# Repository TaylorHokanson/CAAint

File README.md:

# CAAint
An open source badge project for noobs, artists, and the interdimensionally-curious

1. [Project Goals](#project-goals)
2. [BOM](#bom)
2. [Design](#design)
2. [Inspiration](#inspiration)
3. [Team](#team)
4. [Thanks](#thanks)

## Project Goals
We are artists following in the footsteps of the DEFCON [Badgelife](https://hackaday.com/tag/badgelife/) scene. Badgelifers create custom electronic devices to replace the ho-hum badges that display your name and affiliation at conferences. These badges feature playable video games, animated LED displays, wifi connectivity, and more! But what would happen if we released a simple badge template that non-engineers could program and expand upon themselves? Let's find out.

## BOM
After [much experimentation](/Archive), we've settled on [this board](https://www.aliexpress.com/item/TTGO-ESP8266-ESP32-0-96-0-96-inch-OLED-Display-WiFi-Bluetooth-18650-Lithium-Battery-Shield/32839517061.html?spm=a2g0s.9042311.0.0.qXU7bh). It includes the following features in one tidy package:

1. Wifi/bluetooth (via ESP32, the recent update to the ESP8266)
2. LIPO battery clip/recharging circuit
3. Arduino IDE compatibility
4. OLED screen

## Design
After flirting with building a project from scratch, we've brought the process back down to earth. Right now the plan is to focus on a cool little breakout for an existing ESP PCB (see [BOM](#bom)) that will allow for the addition of sensors etc. in the form of pluggable modules. The form-factor could even take the shape of a robot or action figure! Once we release the platform specs, other developers could develop their own modules to extend the project's ecosystem. Ideas include:

1. [Co-planar PCB connectors](https://www.gradconn.com/Products/BoardToBoard/CoPlanarConnectors) ([image](/Media/right_angle_to_right_angle.jpg))
2. [Hemaphroditic connectors](https://octopart.com/10120045-400lf-fci-29441219) ([image](/Media/10120045-400LF.jpg))
3. [5-way tac switch](https://www.aliexpress.com/wholesale?catId=0&initiative_id=AS_20180403080800&SearchText=5+way+tactile+switch)

## Inspiration

1. [P-O-X](https://en.wikipedia.org/wiki/P-O-X) (thanks Paul!)

## Team
Nick Bontrager, Texas Christian University  
Taylor Hokanson, Columbia College Chicago

...and you? Please get in touch!

## Thanks
Supported in part by a generous [Faculty Development Grant](https://about.colum.edu/faculty-development/awards-grants/full-time-development-grants.html) from Columbia College Chicago

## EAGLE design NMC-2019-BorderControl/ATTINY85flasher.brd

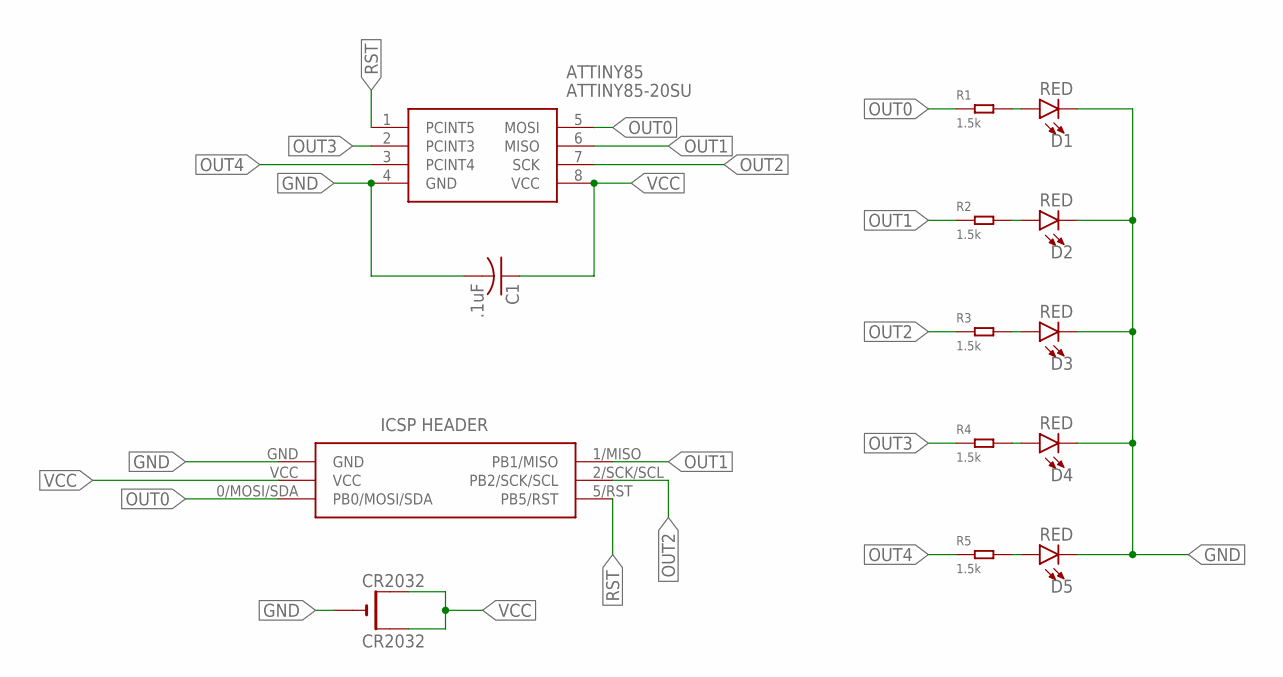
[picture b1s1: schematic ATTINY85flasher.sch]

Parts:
ATTINY85: ATTINY85-20SU; SOT127P798X216-8N
C1: .1uF; C0603
CR2032: CR2032; CR2032-SMD
D1, D2, D3, D4, D5: RED; LED-1206
J1: ICSP-LO-SILK
R1, R2, R3, R4, R5: 1.5k; R1206

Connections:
GND: ATTINY85.4 (GND), C1.2, CR2032.-, D1.C, D2.C, D3.C, D4.C, D5.C, J1.GND
unnamed: D5.A, R5.2
unnamed: D4.A, R4.2
unnamed: D3.A, R3.2
unnamed: D2.A, R2.2
unnamed: D1.A, R1.2
OUT0: ATTINY85.5 (MOSI), J1.0/MOSI/SDA (PB0/MOSI/SDA), R1.1
OUT1: ATTINY85.6 (MISO), J1.1/MISO (PB1/MISO), R2.1
OUT2: ATTINY85.7 (SCK), J1.2/SCK/SCL (PB2/SCK/SCL), R3.1
OUT3: ATTINY85.2 (PCINT3), R4.1
OUT4: ATTINY85.3 (PCINT4), R5.1
RST: ATTINY85.1 (PCINT5), J1.5/RST (PB5/RST)
VCC: ATTINY85.8 (VCC), C1.1, CR2032.+$1 (+), CR2032.+$2 (+1), J1.VCC

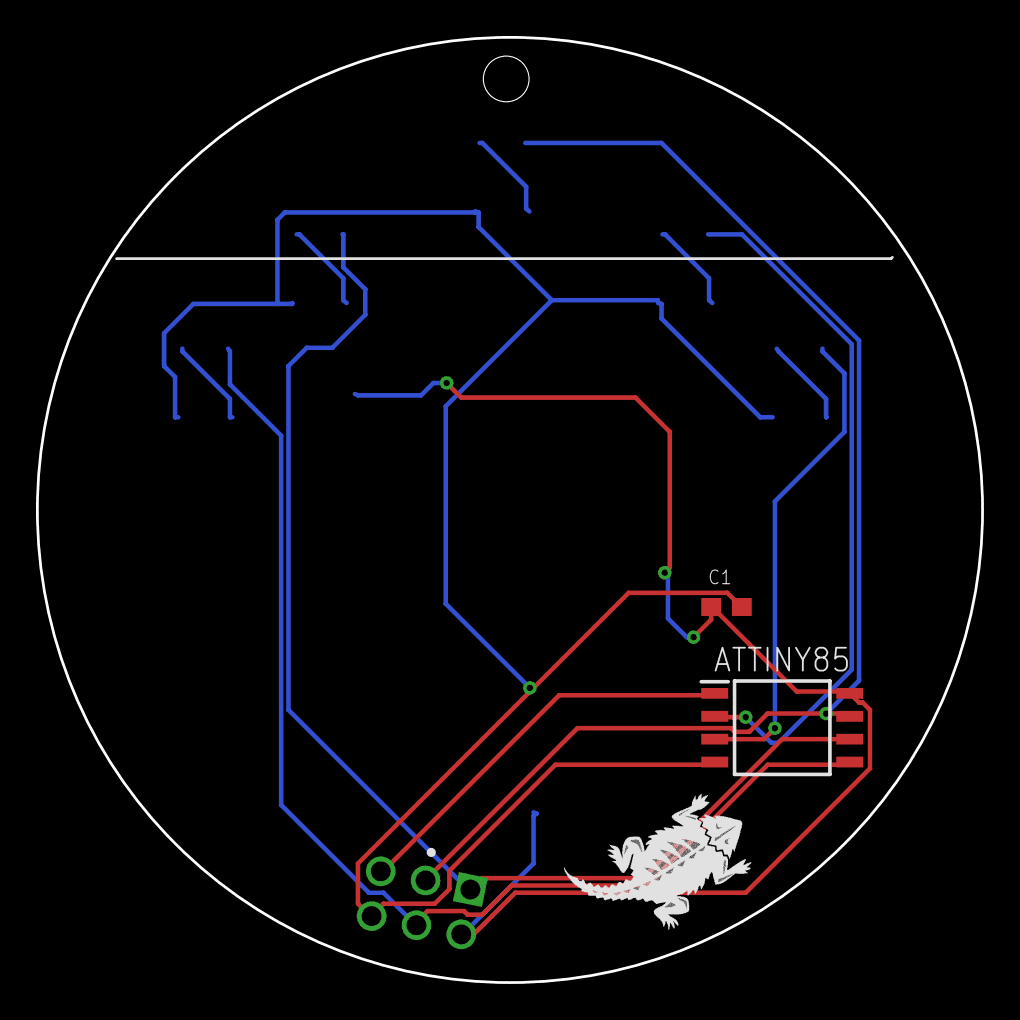
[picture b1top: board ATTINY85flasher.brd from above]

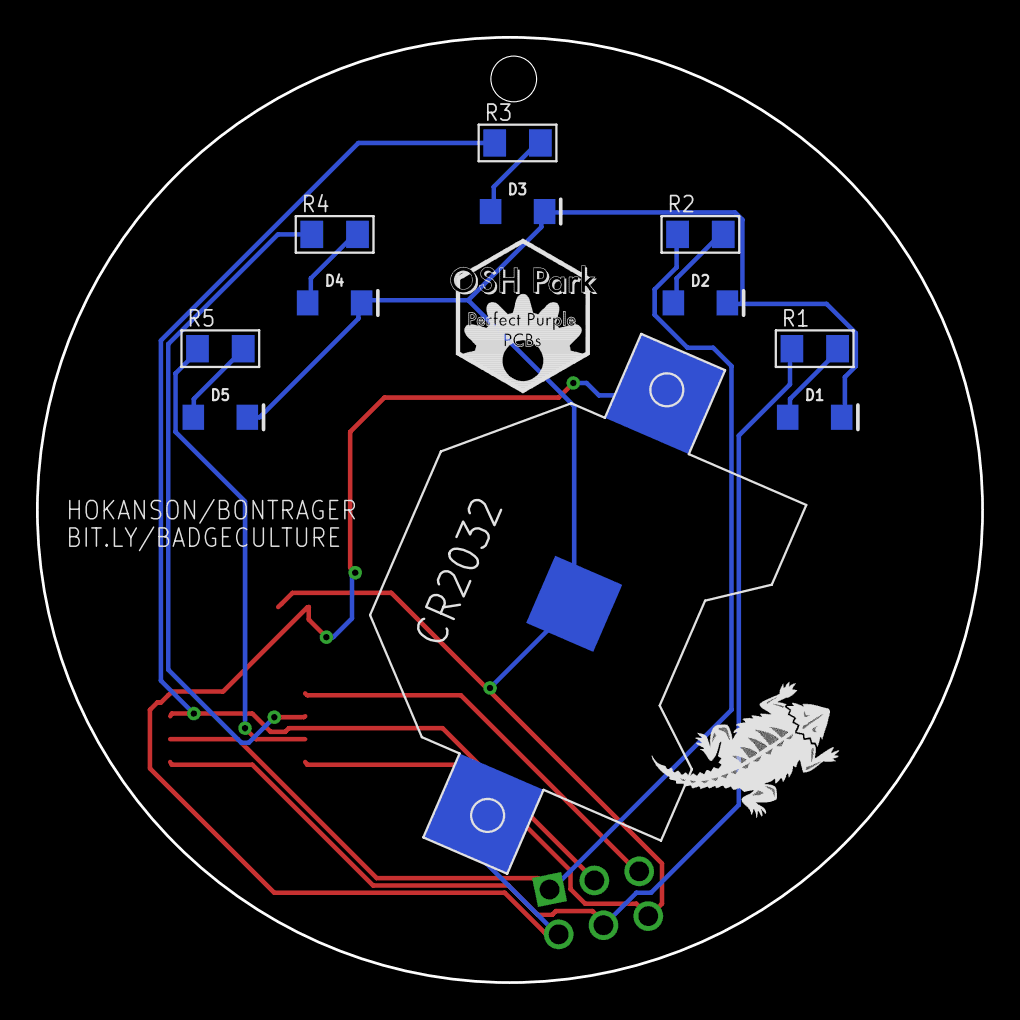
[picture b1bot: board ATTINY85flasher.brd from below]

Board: 2 copper layers, 52.5 x 52.5 mm, 17 parts (13 on the bottom side), 13 nets.

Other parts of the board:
U$1: OSHPARK_LOGOHEX
U$2, U$3: HORNEDFROG

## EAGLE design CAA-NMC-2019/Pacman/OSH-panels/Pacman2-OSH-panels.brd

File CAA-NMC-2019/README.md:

Useful stuff:

MOVE (>0 0) (X Y); to move groups to a new relative X Y position

Board now centered on origin. Use 16.666, 8.333, 4.166, 2.083, and 1.042 grids for general placement.

Changes:

Cleaned up library. Most parts are now defined at library level, including protogrid and power rails. Made custom definition of RGB LEDs so that I could include the cap footprint, this helps prevent endless dragging of multiple parts during layout experiementation. Left the original set in place so that we can verify the wiring transferred OK. Added a switch and two styles of battery mount, switch should isolate bat from USB if both are present (though please check up on my work).

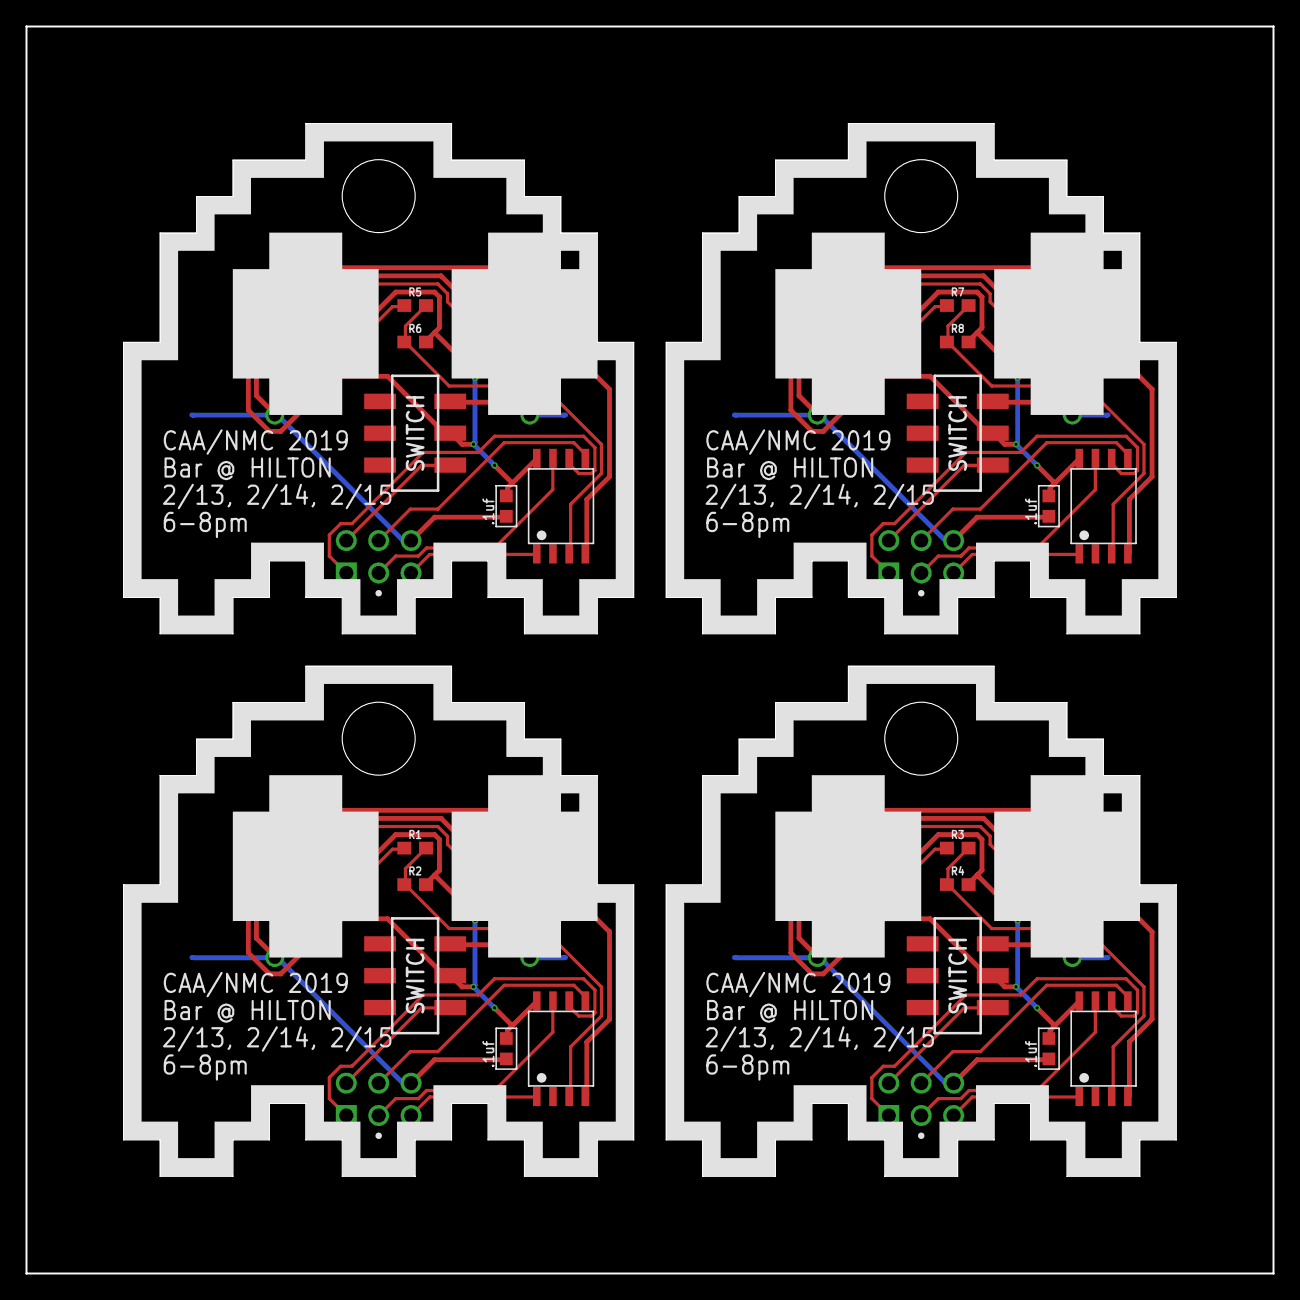
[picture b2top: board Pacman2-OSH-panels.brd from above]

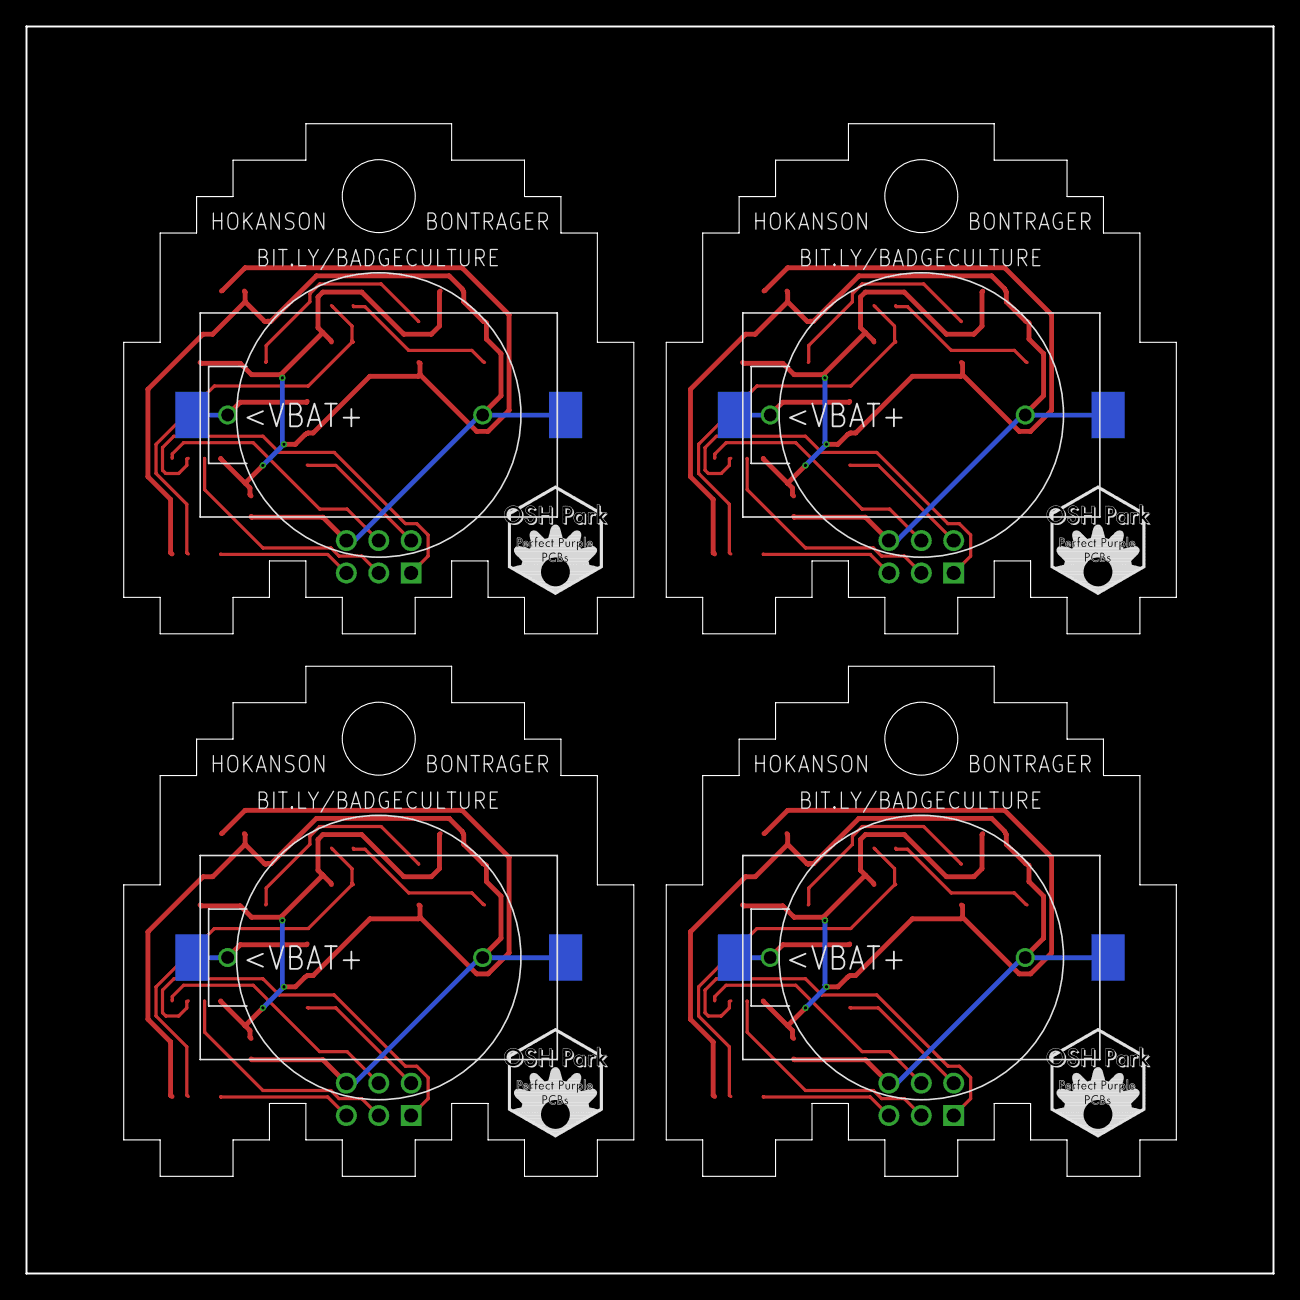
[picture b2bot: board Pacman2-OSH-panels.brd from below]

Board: 2 copper layers, 97.8 x 97.8 mm, 44 parts (12 on the bottom side), 44 nets.

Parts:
D1, D2, D3, D4, D5, D6, D7, D8: WS2812B
DECOUPLER, DECOUPLER1, DECOUPLER2, DECOUPLER3: .1uf; 0603-CAP
IC1, IC2, IC3, IC4: ATTINY85-20SU; SOT127P798X216-8N
J1, J2, J3, J4: ICSP-LO-SILK
R1, R3, R5, R7: 470; 0603
R2, R4, R6, R8: 10k; 0603
U$1, U$8, U$12, U$145: SMT-SWITCH
U$2, U$4, U$9, U$13: SMT-BATTERY-HOLDER; SMT-CR-HOLDER
U$3, U$6, U$10, U$14: THRU-CR-HOLDER
U$5, U$7, U$11, U$15: OSHPARK_LOGOHEX

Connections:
GND: D1.CAP1, D1.GND, D2.CAP1, D2.GND, DECOUPLER.CAP1, IC1.GND, J2.GND, U$2.GND, U$3.GND
GND1: D3.CAP1, D3.GND, D4.CAP1, D4.GND, DECOUPLER1.CAP1, IC2.GND, J1.GND, U$4.GND, U$6.GND
GND2: D5.CAP1, D5.GND, D6.CAP1, D6.GND, DECOUPLER2.CAP1, IC3.GND, J3.GND, U$9.GND, U$10.GND
GND3: D7.CAP1, D7.GND, D8.CAP1, D8.GND, DECOUPLER3.CAP1, IC4.GND, J4.GND, U$13.GND, U$14.GND
unnamed: D3.DO, D4.DI
unnamed: D3.DI, R3.1
unnamed: D1.DO, D2.DI
unnamed: D5.DO, D6.DI
unnamed: D1.DI, R1.1
unnamed: D5.DI, R5.1
unnamed: D7.DO, D8.DI
unnamed: D7.DI, R7.1
PB0: IC1.PB0, J2.0/MOSI/SDA
PB1: IC1.PB1, J2.1/MISO
PB2: IC1.PB2, J2.2/SCK/SCL
PB4: IC1.PB4, R1.2, R2.1
PB5: IC1.PB5, J2.5/RST
PB6: IC2.PB0, J1.0/MOSI/SDA
PB8: IC2.PB4, R3.2, R4.1
PB9: IC2.PB2, J1.2/SCK/SCL
PB10: IC2.PB5, J1.5/RST
PB11: IC2.PB1, J1.1/MISO
PB12: IC3.PB0, J3.0/MOSI/SDA
PB14: IC3.PB4, R5.2, R6.1
PB15: IC3.PB2, J3.2/SCK/SCL
PB16: IC3.PB5, J3.5/RST
PB17: IC3.PB1, J3.1/MISO
PB18: IC4.PB0, J4.0/MOSI/SDA
PB20: IC4.PB4, R7.2, R8.1
PB21: IC4.PB2, J4.2/SCK/SCL
PB22: IC4.PB5, J4.5/RST
PB23: IC4.PB1, J4.1/MISO
VBAT: U$2.VBAT, U$3.VBAT, U$145.4
VBAT1: U$1.4, U$4.VBAT, U$6.VBAT
VBAT2: U$8.4, U$9.VBAT, U$10.VBAT
VBAT3: U$12.4, U$13.VBAT, U$14.VBAT
VCC: D1.CAP2, D1.VCC, D2.CAP2, D2.VCC, DECOUPLER.CAP2, IC1.VCC, R2.2, U$145.5
VCC1: D3.CAP2, D3.VCC, D4.CAP2, D4.VCC, DECOUPLER1.CAP2, IC2.VCC, R4.2, U$1.5
VCC2: D5.CAP2, D5.VCC, D6.CAP2, D6.VCC, DECOUPLER2.CAP2, IC3.VCC, R6.2, U$8.5
VCC3: D7.CAP2, D7.VCC, D8.CAP2, D8.VCC, DECOUPLER3.CAP2, IC4.VCC, R8.2, U$12.5
VUSB: J2.VCC, U$145.6
VUSB1: J1.VCC, U$1.6
VUSB2: J3.VCC, U$8.6
VUSB3: J4.VCC, U$12.6

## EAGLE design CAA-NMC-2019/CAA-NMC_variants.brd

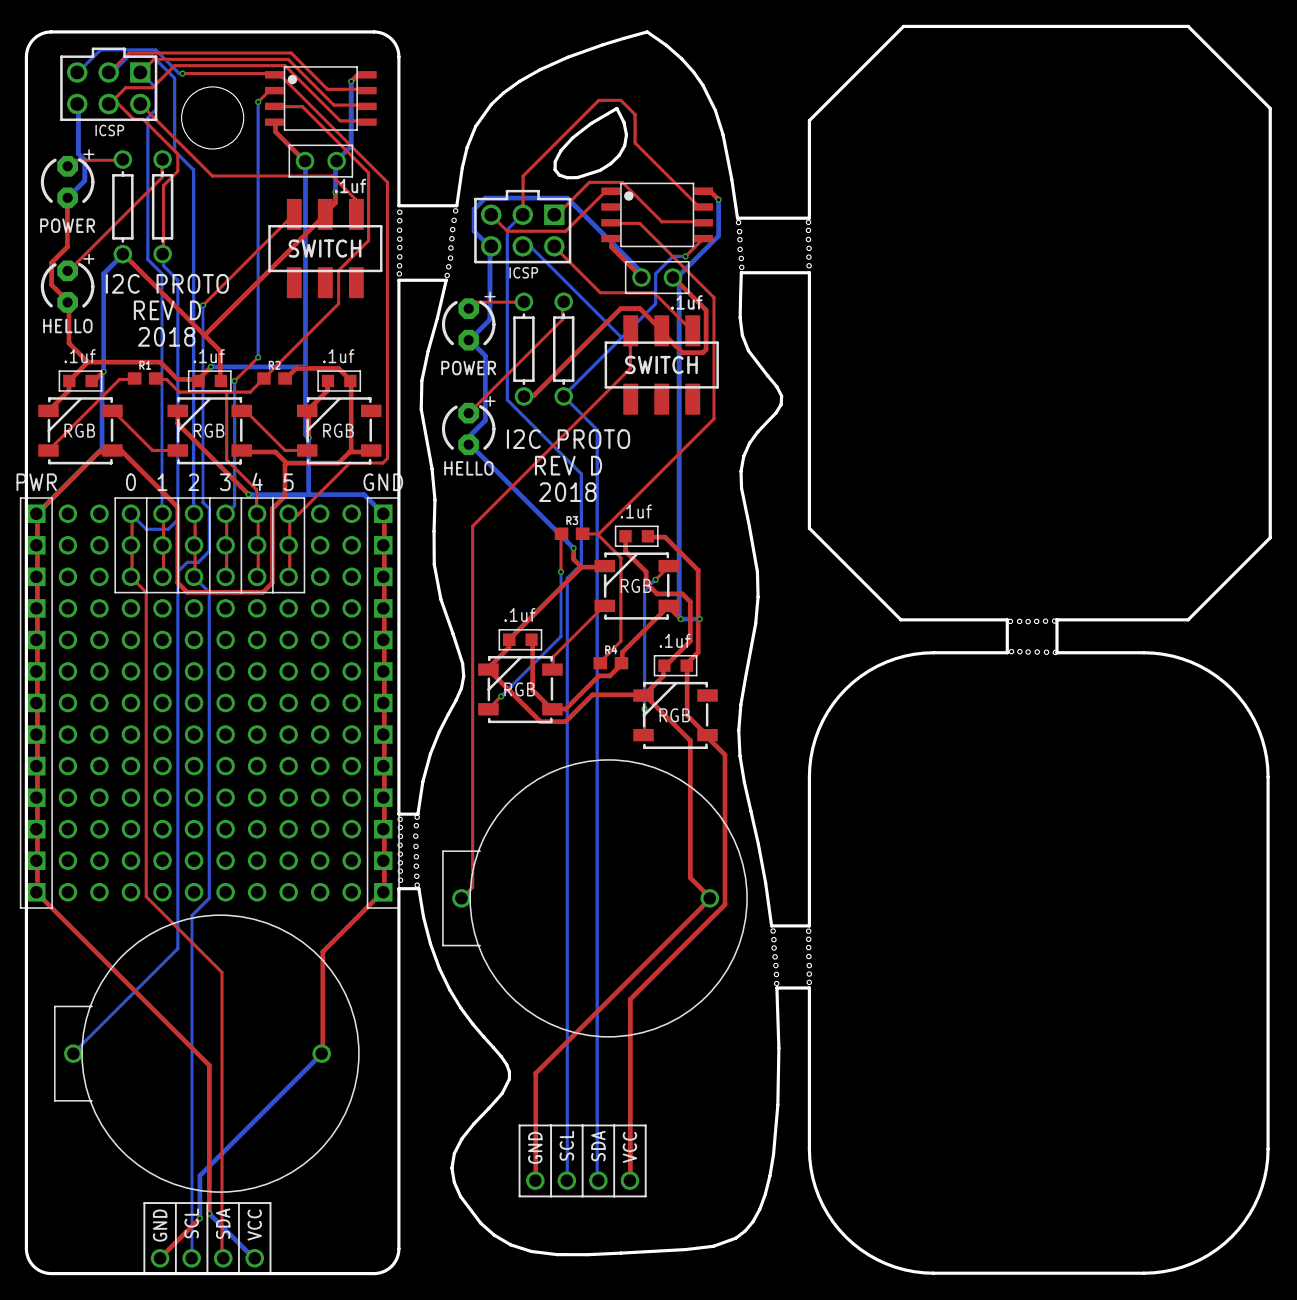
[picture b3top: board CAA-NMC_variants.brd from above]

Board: 2 copper layers, 100.2 x 100.4 mm, 37 parts (0 on the bottom side), 29 nets.

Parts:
D1, D2, D3, D4, D5, D6: WS2812B
HELLO, HELLO1: LED3MM
IC1, IC2: ATTINY85-20SU; SOT127P798X216-8N
J1, J2: M20-9980346; HDRV6W64P254_2X3_762X508X868P
POWER, POWER1: LED3MM
R1, R3: 470; 0603
R2, R4: 10k; 0603
U$1: PROTO
U$3, U$14: THRU-CR-HOLDER
U$4, U$71: GND; 1X01
U$5, U$74: VCC; 1X01
U$6, U$72: SDA; 1X01
U$7, U$73: SCL; 1X01
U$8, U$123: DECOUPLING_CAP
U$9, U$10, U$126, U$127: RESISTOR; AXIAL-0.3
U$11, U$145: SMT-SWITCH

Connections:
GND: D1.CAP1, D1.GND, D2.CAP1, D2.GND, D3.CAP1, D3.GND, HELLO.NEG, IC1.GND, J1.GND, POWER.NEG, U$1.GND0, U$1.GND1, U$1.GND2, U$1.GND3, U$1.GND4, U$1.GND5, U$1.GND6, U$1.GND7, U$1.GND8, U$1.GND9, U$1.GND10, U$1.GND11, U$1.GND12, U$3.GND, U$71.P$1, U$123.P$1
GND1: D4.CAP1, D4.GND, D5.CAP1, D5.GND, D6.CAP1, D6.GND, HELLO1.NEG, IC2.GND, J2.GND, POWER1.NEG, U$4.P$1, U$8.P$1, U$14.GND
unnamed: POWER.POS, U$126.P$3
unnamed: HELLO.POS, U$127.P$3
unnamed: D1.DO, D2.DI
unnamed: D2.DO, D3.DI
unnamed: D1.DI, R1.1
unnamed: POWER1.POS, U$9.P$3
unnamed: HELLO1.POS, U$10.P$3
unnamed: D4.DO, D5.DI
unnamed: D5.DO, D6.DI
unnamed: D4.DI, R3.1
PB0: IC1.PB0, J1.0/MOSI/SDA, U$1.0A, U$1.0B, U$1.0C, U$72.P$1, U$127.P$4
PB1: IC1.PB1, J1.1/MISO, U$1.1A, U$1.1B, U$1.1C
PB2: IC1.PB2, J1.2/SCK/SCL, U$1.2A, U$1.2B, U$1.2C, U$73.P$1
PB3: IC1.PB3, U$1.3A, U$1.3B, U$1.3C
PB4: IC1.PB4, R1.2, R2.1, U$1.4A, U$1.4B, U$1.4C
PB5: IC1.PB5, J1.5/RST, U$1.5A, U$1.5B, U$1.5C
PB6: IC2.PB0, J2.0/MOSI/SDA, U$6.P$1, U$10.P$4
PB8: IC2.PB4, R3.2, R4.1
PB9: IC2.PB2, J2.2/SCK/SCL, U$7.P$1
PB10: IC2.PB5, J2.5/RST
PB11: IC2.PB1, J2.1/MISO
VBAT: U$3.VBAT, U$145.4
VBAT1: U$11.4, U$14.VBAT
VCC: D1.CAP2, D1.VCC, D2.CAP2, D2.VCC, D3.CAP2, D3.VCC, IC1.VCC, R2.2, U$1.PWR0, U$1.PWR1, U$1.PWR2, U$1.PWR3, U$1.PWR4, U$1.PWR5, U$1.PWR6, U$1.PWR7, U$1.PWR8, U$1.PWR9, U$1.PWR10, U$1.PWR11, U$1.PWR12, U$74.P$1, U$123.P$2, U$126.P$4, U$145.5
VCC1: D4.CAP2, D4.VCC, D5.CAP2, D5.VCC, D6.CAP2, D6.VCC, IC2.VCC, R4.2, U$5.P$1, U$8.P$2, U$9.P$4, U$11.5
VUSB: J1.VCC, U$145.6
VUSB1: J2.VCC, U$11.6

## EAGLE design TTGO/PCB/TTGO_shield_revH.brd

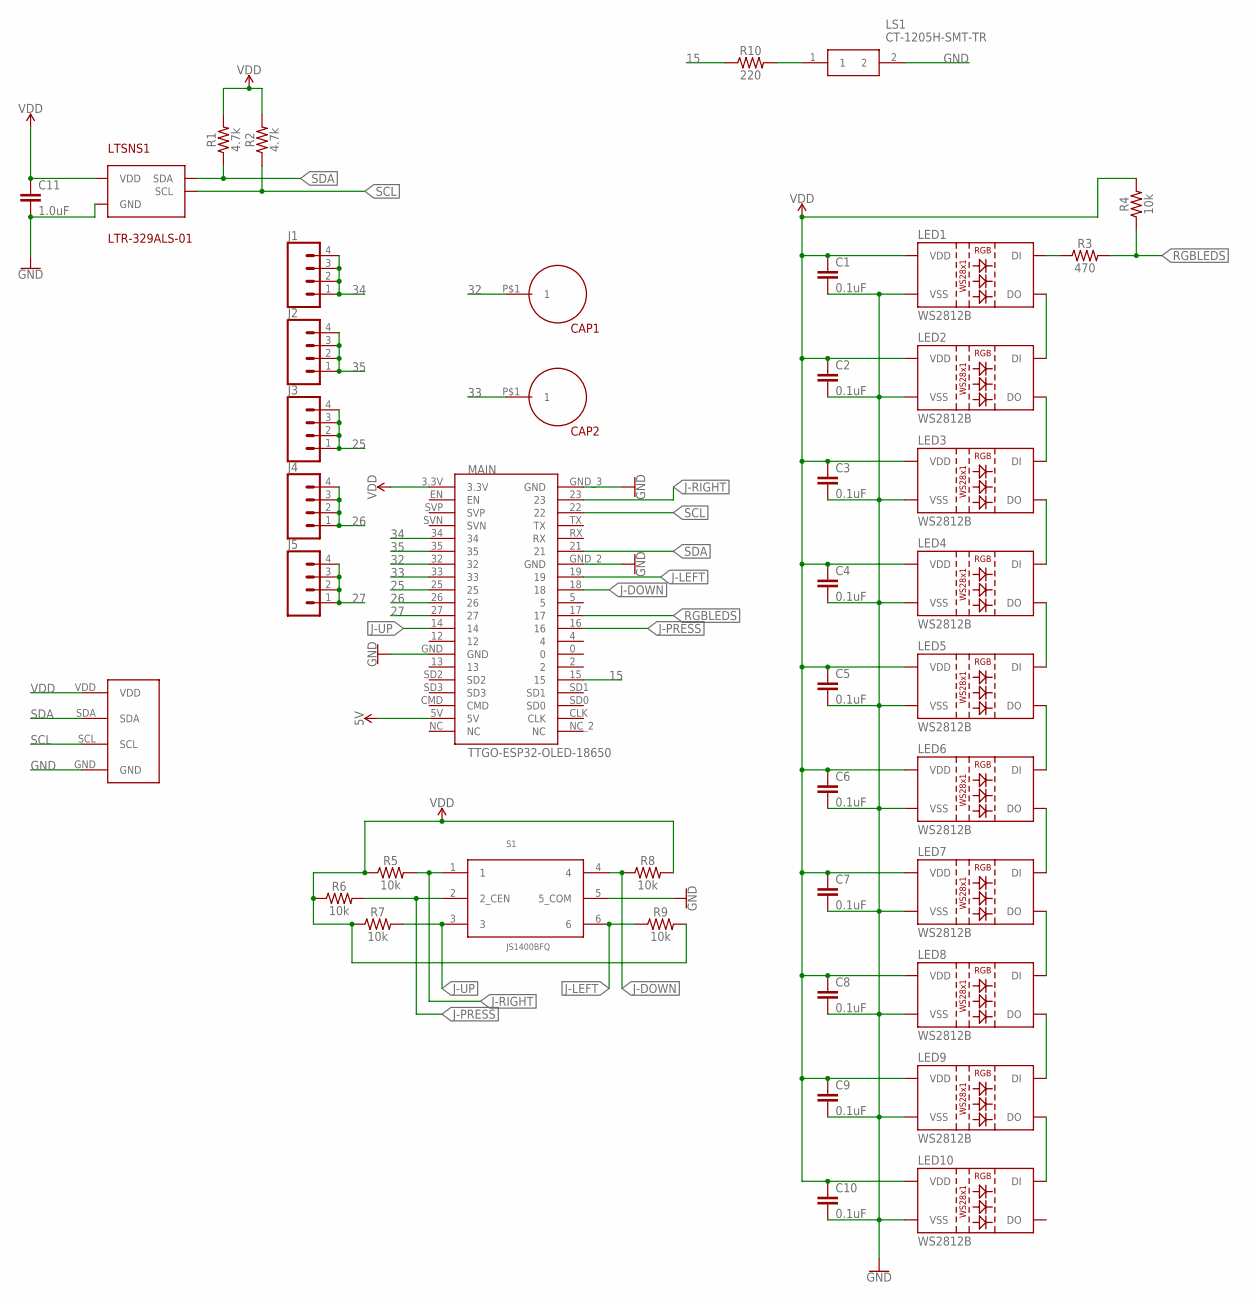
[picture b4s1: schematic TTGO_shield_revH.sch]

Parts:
C1, C2, C3, C4, C5, C6, C7, C8, C9, C10: 0.1uF; 0603
C11: 1.0uF; 0805
CAP1, CAP2: CAPSENSE_BUTTON
J1, J2, J3, J4, J5: CONN_04LONGPADS; 1X04_LONGPADS
LED1, LED2, LED3, LED4, LED5, LED6, LED7, LED8, LED9, LED10: WS2812B
LS1: CT-1205H-SMT-TR; CT1205HSMTTR
LTSNS1: LTR-329ALS-01; CHIPLED-4
MAIN: TTGO-ESP32-OLED-18650
R1, R2: 4.7k; 0603
R3: 470; 0603
R4, R5, R6, R7, R8, R9: 10k; 0603
R10: 220; 0603
S1: JS1400BFQ
U$2: I2C-FEMALE-HEADER

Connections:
5V: MAIN.5V
15: MAIN.15, R10.1
25: J3.1, J3.2, J3.3, J3.4, MAIN.25
26: J4.1, J4.2, J4.3, J4.4, MAIN.26
27: J5.1, J5.2, J5.3, J5.4, MAIN.27
32: CAP1.P$1, MAIN.32
33: CAP2.P$1, MAIN.33
34: J1.1, J1.2, J1.3, J1.4, MAIN.34
35: J2.1, J2.2, J2.3, J2.4, MAIN.35
GND: C1.2, C2.2, C3.2, C4.2, C5.2, C6.2, C7.2, C8.2, C9.2, C10.2, C11.2, LED1.3 (VSS), LED2.3 (VSS), LED3.3 (VSS), LED4.3 (VSS), LED5.3 (VSS), LED6.3 (VSS), LED7.3 (VSS), LED8.3 (VSS), LED9.3 (VSS), LED10.3 (VSS), LS1.2, LTSNS1.2 (GND), MAIN.GND, MAIN.GND_2 (GND), MAIN.GND_3 (GND), S1.5 (5_COM), U$2.GND
J-DOWN: MAIN.18, R8.1, S1.4
J-LEFT: MAIN.19, R9.1, S1.6
J-PRESS: MAIN.16, R6.2, S1.2 (2_CEN)
J-RIGHT: MAIN.23, R5.2, S1.1
J-UP: MAIN.14, R7.2, S1.3
unnamed: LED5.2 (DO), LED6.4 (DI)
unnamed: LED6.2 (DO), LED7.4 (DI)
unnamed: LED7.2 (DO), LED8.4 (DI)
unnamed: LED8.2 (DO), LED9.4 (DI)
unnamed: LED4.2 (DO), LED5.4 (DI)
unnamed: LED9.2 (DO), LED10.4 (DI)
unnamed: LS1.1, R10.2
unnamed: LED1.2 (DO), LED2.4 (DI)
unnamed: LED2.2 (DO), LED3.4 (DI)
unnamed: LED3.2 (DO), LED4.4 (DI)
unnamed: LED1.4 (DI), R3.1
RGBLEDS: MAIN.17, R3.2, R4.1
SCL: LTSNS1.4 (SCL), MAIN.22, R2.1, U$2.SCL
SDA: LTSNS1.3 (SDA), MAIN.21, R1.1, U$2.SDA
VDD: C1.1, C2.1, C3.1, C4.1, C5.1, C6.1, C7.1, C8.1, C9.1, C10.1, C11.1, LED1.1 (VDD), LED2.1 (VDD), LED3.1 (VDD), LED4.1 (VDD), LED5.1 (VDD), LED6.1 (VDD), LED7.1 (VDD), LED8.1 (VDD), LED9.1 (VDD), LED10.1 (VDD), LTSNS1.1 (VDD), MAIN.3.3V, R1.2, R2.2, R4.2, R5.1, R6.1, R7.1, R8.2, R9.2, U$2.VDD

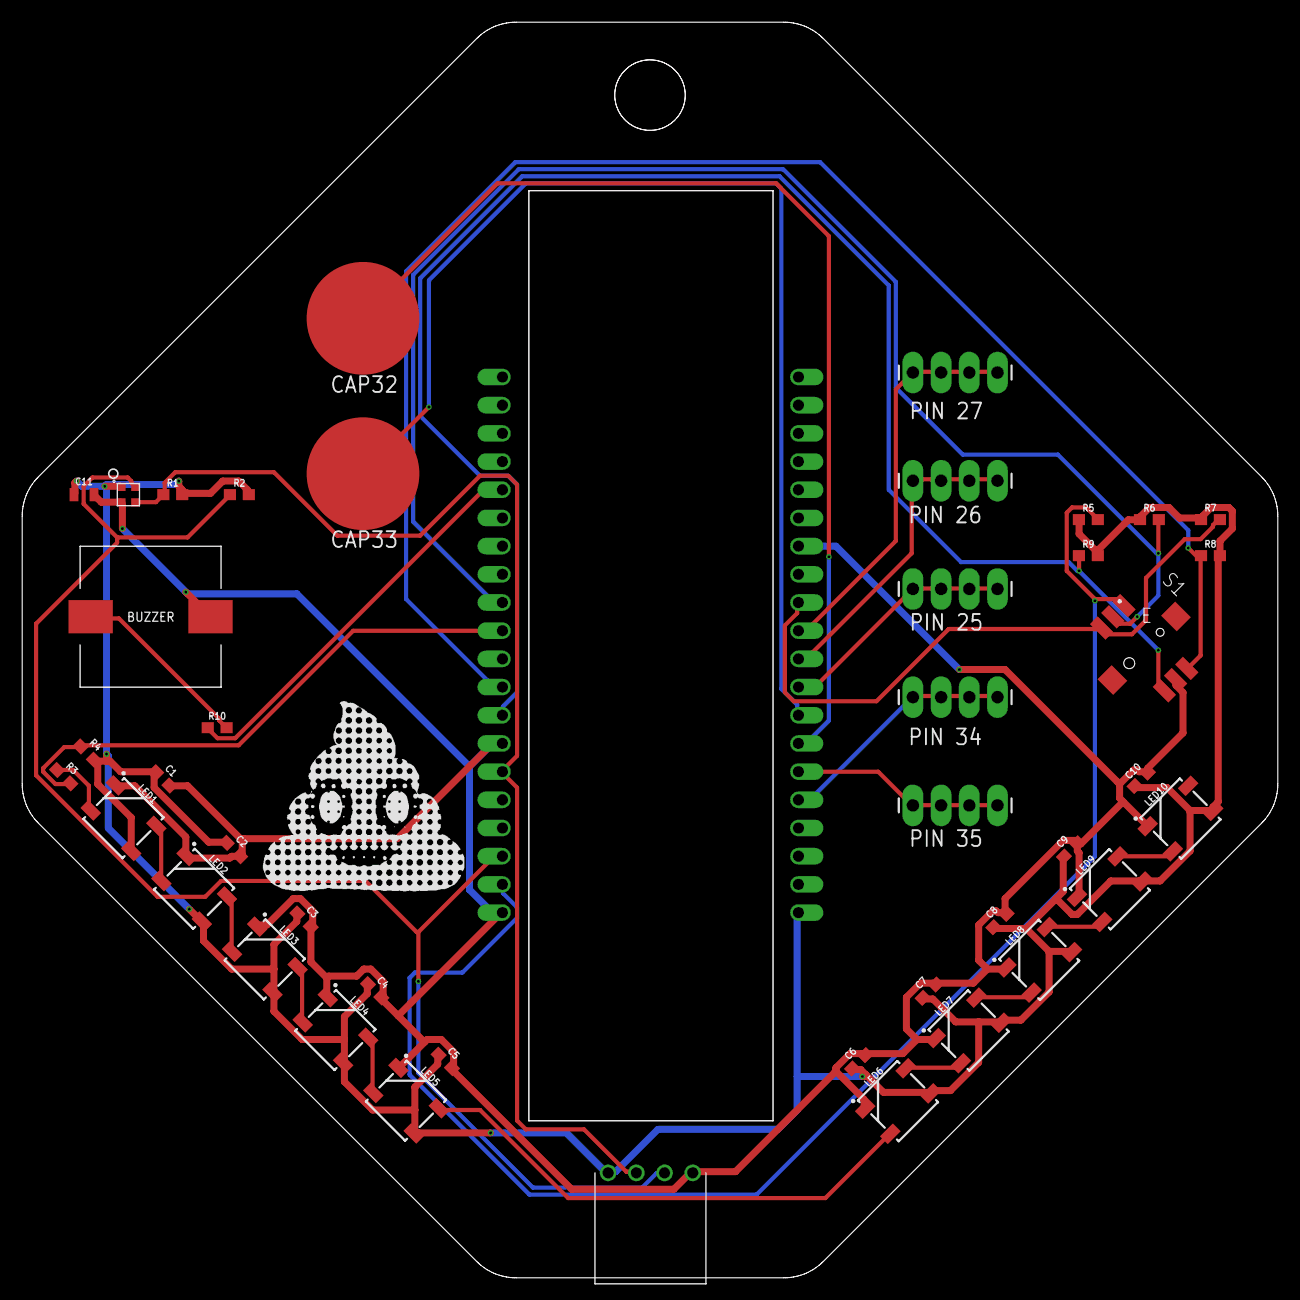
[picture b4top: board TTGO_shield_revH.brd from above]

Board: 2 copper layers, 113.1 x 113.1 mm, 43 parts (0 on the bottom side), 29 nets.

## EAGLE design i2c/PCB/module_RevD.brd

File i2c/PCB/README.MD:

##Seeed Fusion PCB Design Notes
Some of the following are hard and fast rules. Others are just there to qualify for a discount.

1. 100 x 100 mm
2. Panelized designs can only feature two variations
3. Smallest trace/clearance is 6/6 mil
   - Work larger whenever possible
   - Edit > Net Classes to establish t/c families
      - defaults 10/10 mil
      - VCC/GND 25/10 mil
4. Circuit-to-edge: .3mm
5. Circuit-to-V groove: .8mm
   - Seeed DRC will not catch this
   - Measured from V groove centerline
    - Our modified Seeed DRC has a Distance > Copper/Dimension of 40mil to account for this omission

##Eagle Design Notes
1. TBA

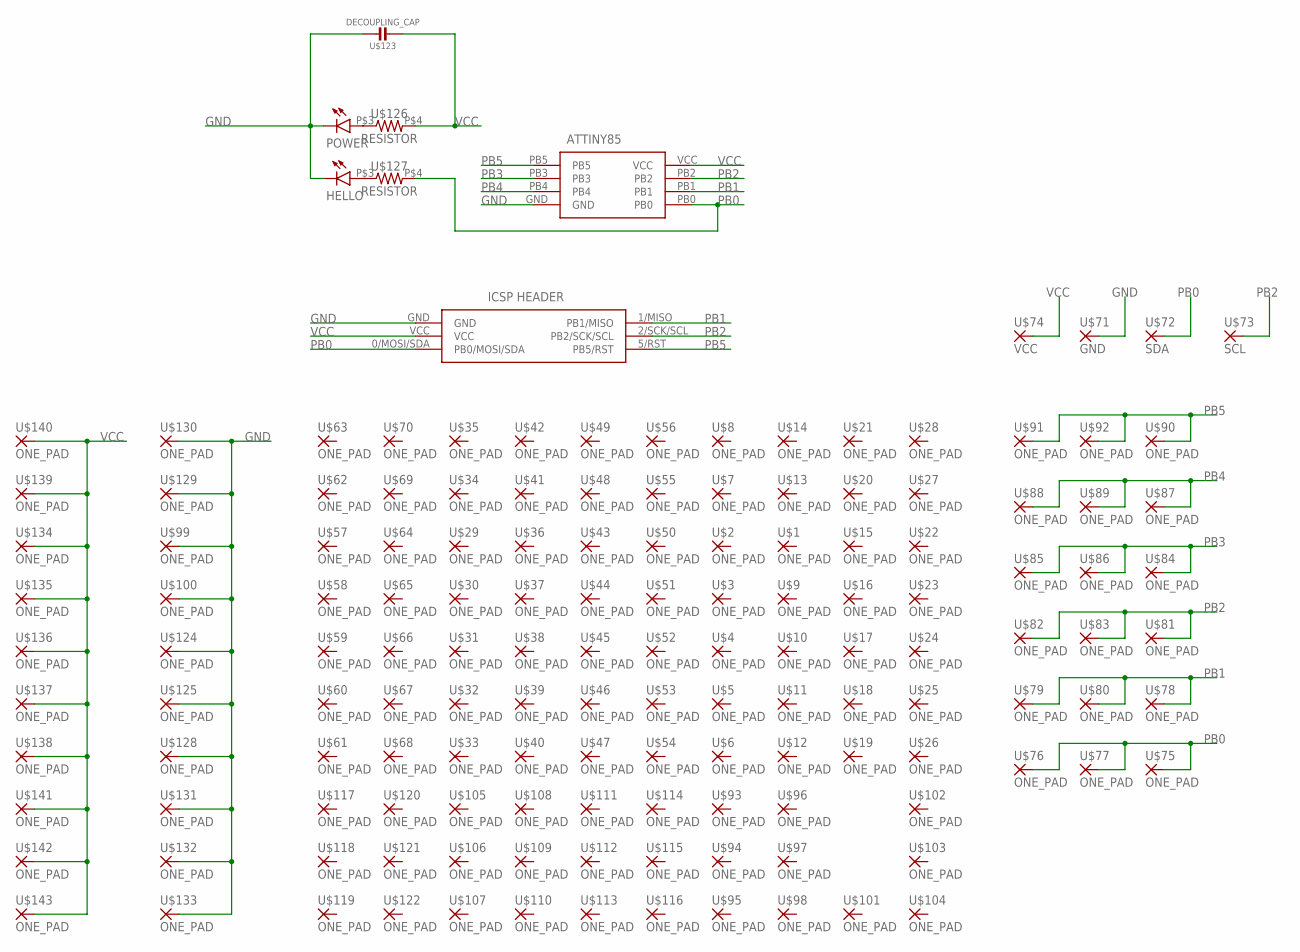
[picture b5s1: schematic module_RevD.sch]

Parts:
HELLO: LED3MM
IC1: ATTINY85-20SU; SOT127P798X216-8N
J1: M20-9980346; HDRV6W64P254_2X3_762X508X868P
POWER: LED3MM
U$1, U$2, U$3, U$4, U$5, U$6, U$7, U$8, U$9, U$10, U$11, U$12, U$13, U$14, U$15, U$16, U$17, U$18, U$19, U$20, U$21, U$22, U$23, U$24, U$25, U$26, U$27, U$28, U$29, U$30, U$31, U$32, U$33, U$34, U$35, U$36, U$37, U$38, U$39, U$40, U$41, U$42, U$43, U$44, U$45, U$46, U$47, U$48, U$49, U$50, U$51, U$52, U$53, U$54, U$55, U$56, U$57, U$58, U$59, U$60, U$61, U$62, U$63, U$64, U$65, U$66, U$67, U$68, U$69, U$70, U$75, U$76, U$77, U$78, U$79, U$80, U$81, U$82, U$83, U$84, U$85, U$86, U$87, U$88, U$89, U$90, U$91, U$92, U$93, U$94, U$95, U$96, U$97, U$98, U$99, U$100, U$101, U$102, U$103, U$104, U$105, U$106, U$107, U$108, U$109, U$110, U$111, U$112, U$113, U$114, U$115, U$116, U$117, U$118, U$119, U$120, U$121, U$122, U$124, U$125, U$128, U$129, U$130, U$131, U$132, U$133, U$134, U$135, U$136, U$137, U$138, U$139, U$140, U$141, U$142, U$143: ONE_PAD; 1X01
U$71: GND; 1X01
U$72: SDA; 1X01
U$73: SCL; 1X01
U$74: VCC; 1X01
U$123: DECOUPLING_CAP
U$126, U$127: RESISTOR; AXIAL-0.3

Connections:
GND: HELLO.NEG, IC1.GND, J1.GND, POWER.NEG, U$71.P$1, U$99.P$1, U$100.P$1, U$123.P$1 (1), U$124.P$1, U$125.P$1, U$128.P$1, U$129.P$1, U$130.P$1, U$131.P$1, U$132.P$1, U$133.P$1
unnamed: POWER.POS, U$126.P$3 (1)
unnamed: HELLO.POS, U$127.P$3 (1)
PB0: IC1.PB0, J1.0/MOSI/SDA (PB0/MOSI/SDA), U$72.P$1, U$75.P$1, U$76.P$1, U$77.P$1, U$127.P$4 (2)
PB1: IC1.PB1, J1.1/MISO (PB1/MISO), U$78.P$1, U$79.P$1, U$80.P$1
PB2: IC1.PB2, J1.2/SCK/SCL (PB2/SCK/SCL), U$73.P$1, U$81.P$1, U$82.P$1, U$83.P$1
PB3: IC1.PB3, U$84.P$1, U$85.P$1, U$86.P$1
PB4: IC1.PB4, U$87.P$1, U$88.P$1, U$89.P$1
PB5: IC1.PB5, J1.5/RST (PB5/RST), U$90.P$1, U$91.P$1, U$92.P$1
VCC: IC1.VCC, J1.VCC, U$74.P$1, U$123.P$2 (2), U$126.P$4 (2), U$134.P$1, U$135.P$1, U$136.P$1, U$137.P$1, U$138.P$1, U$139.P$1, U$140.P$1, U$141.P$1, U$142.P$1, U$143.P$1

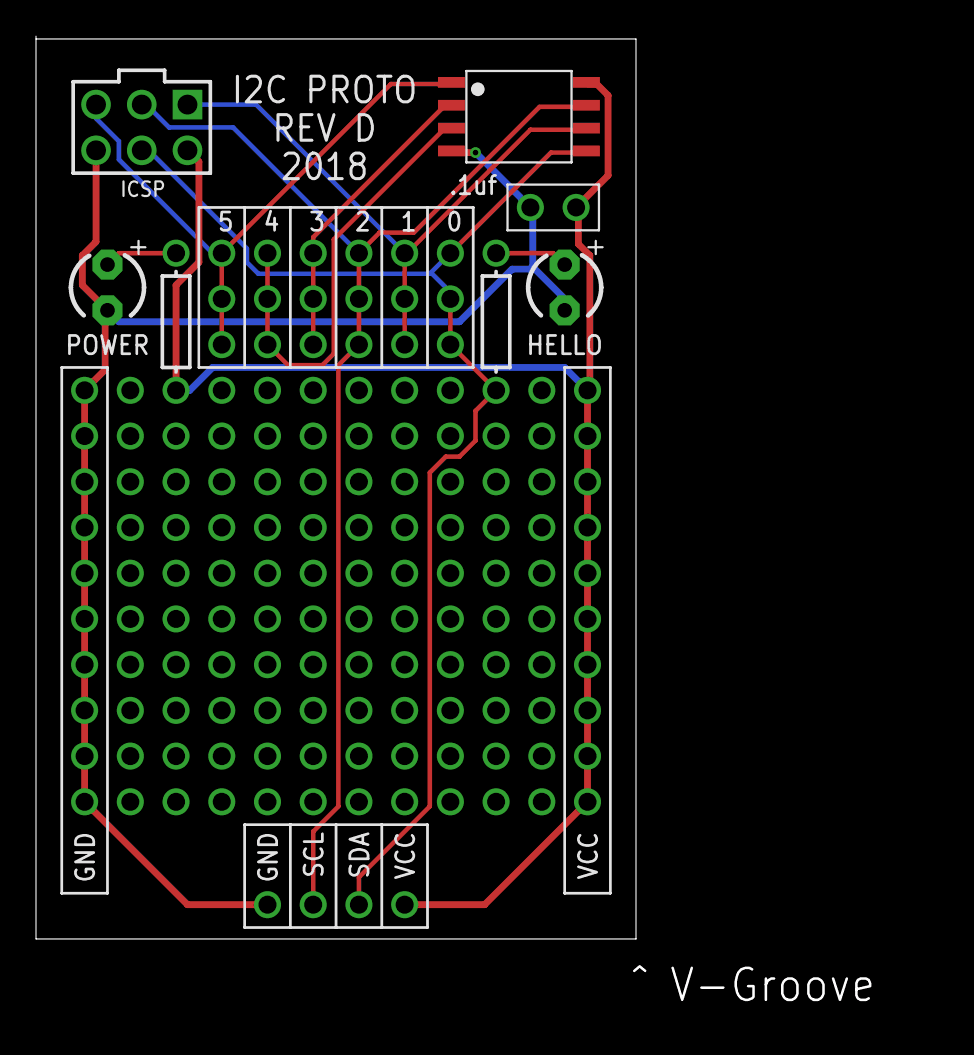
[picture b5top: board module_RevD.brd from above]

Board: 2 copper layers, 33.3 x 50.2 mm, 147 parts (0 on the bottom side), 10 nets.

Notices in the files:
parts and their libraries:
SparkFun-Resistors: Licensing: Creative Commons ShareAlike 4.0 International - https://creativecommons.org/licenses/by-sa/4.0
